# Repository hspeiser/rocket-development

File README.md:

# rocket dev
custom board and code that runs a rpi pico and a NRF24L01 that ignites a rocket motor from far away wirelessly

hx711 w/ 20kg load cell readings using rpi pico

motor simulation characteristics

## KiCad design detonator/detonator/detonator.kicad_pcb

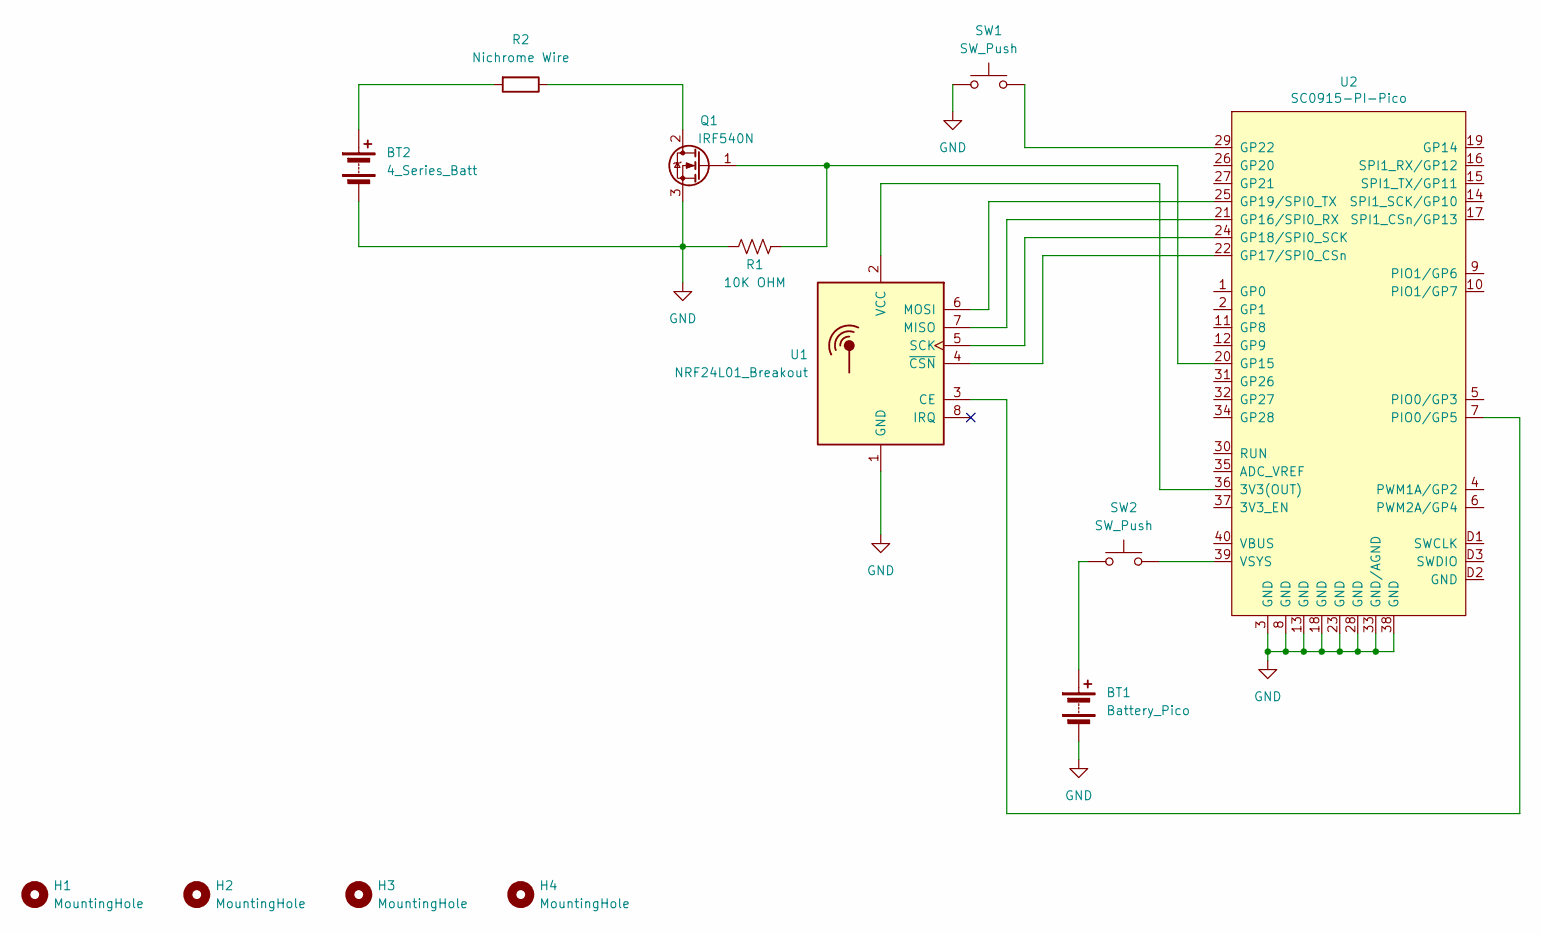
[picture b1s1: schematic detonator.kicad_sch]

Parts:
BT1: Battery_Pico; CONN_2604-1102_WAG
BT2: 4_Series_Batt; CONN_2604-1102_WAG
H1, H2, H3, H4: MountingHole; MountingHole_3.5mm
Q1: IRF540N; TO-220-3_Vertical
R1: 10K OHM; R_Axial_DIN0207_L6.3mm_D2.5mm_P5.08mm_Vertical
R2: Nichrome Wire; CONN_2604-1102_WAG
SW1, SW2: SW_Push; R_Axial_DIN0207_L6.3mm_D2.5mm_P5.08mm_Vertical
U1: NRF24L01_Breakout; nRF24L01_Breakout
U2: SC0915-PI-Pico; PICO

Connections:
GND: BT1.2 (-), BT2.2 (-), Q1.3 (S), R1.1, SW1.1, U1.1 (GND), U2.3 (GND), U2.8 (GND), U2.13 (GND), U2.18 (GND), U2.23 (GND), U2.28 (GND), U2.33 (GND/AGND), U2.38 (GND)
unnamed: BT1.1 (+), SW2.1
unnamed: BT2.1 (+), R2.2
unnamed: Q1.2 (D), R2.1
unnamed: Q1.1 (G), R1.2, U2.20 (GP15)
unnamed: U1.3 (CE), U2.7 (PIO0/GP5)
unnamed: U1.7 (MISO), U2.21 (GP16/SPI0_RX)
unnamed: U1.6 (MOSI), U2.25 (GP19/SPI0_TX)
unnamed: U1.5 (SCK), U2.24 (GP18/SPI0_SCK)
unnamed: U1.2 (VCC), U2.36 (3V3(OUT))
unnamed: U1.4 (~CSN), U2.22 (GP17/SPI0_CSn)
unnamed: SW1.2, U2.29 (GP22)
unnamed: SW2.2, U2.39 (VSYS)

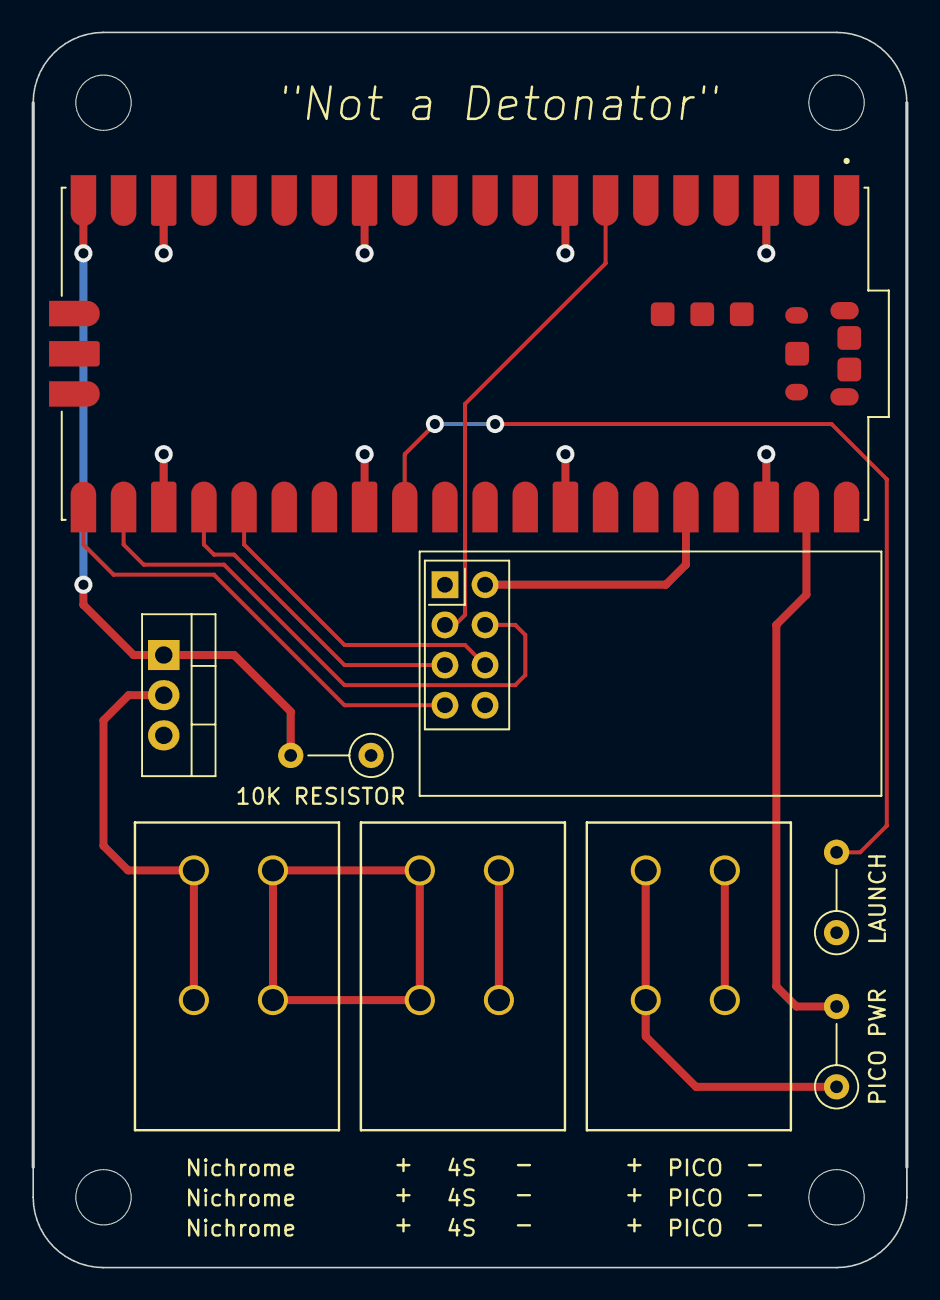
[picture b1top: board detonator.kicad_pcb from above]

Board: 2 copper layers, 55.2 x 78.0 mm, 13 parts (0 on the bottom side), 13 nets.

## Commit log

2024-09-14 adding main files
